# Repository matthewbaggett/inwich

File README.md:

# inwich
A PCB and software to allow a PC to push joypad commands to a console via USB.

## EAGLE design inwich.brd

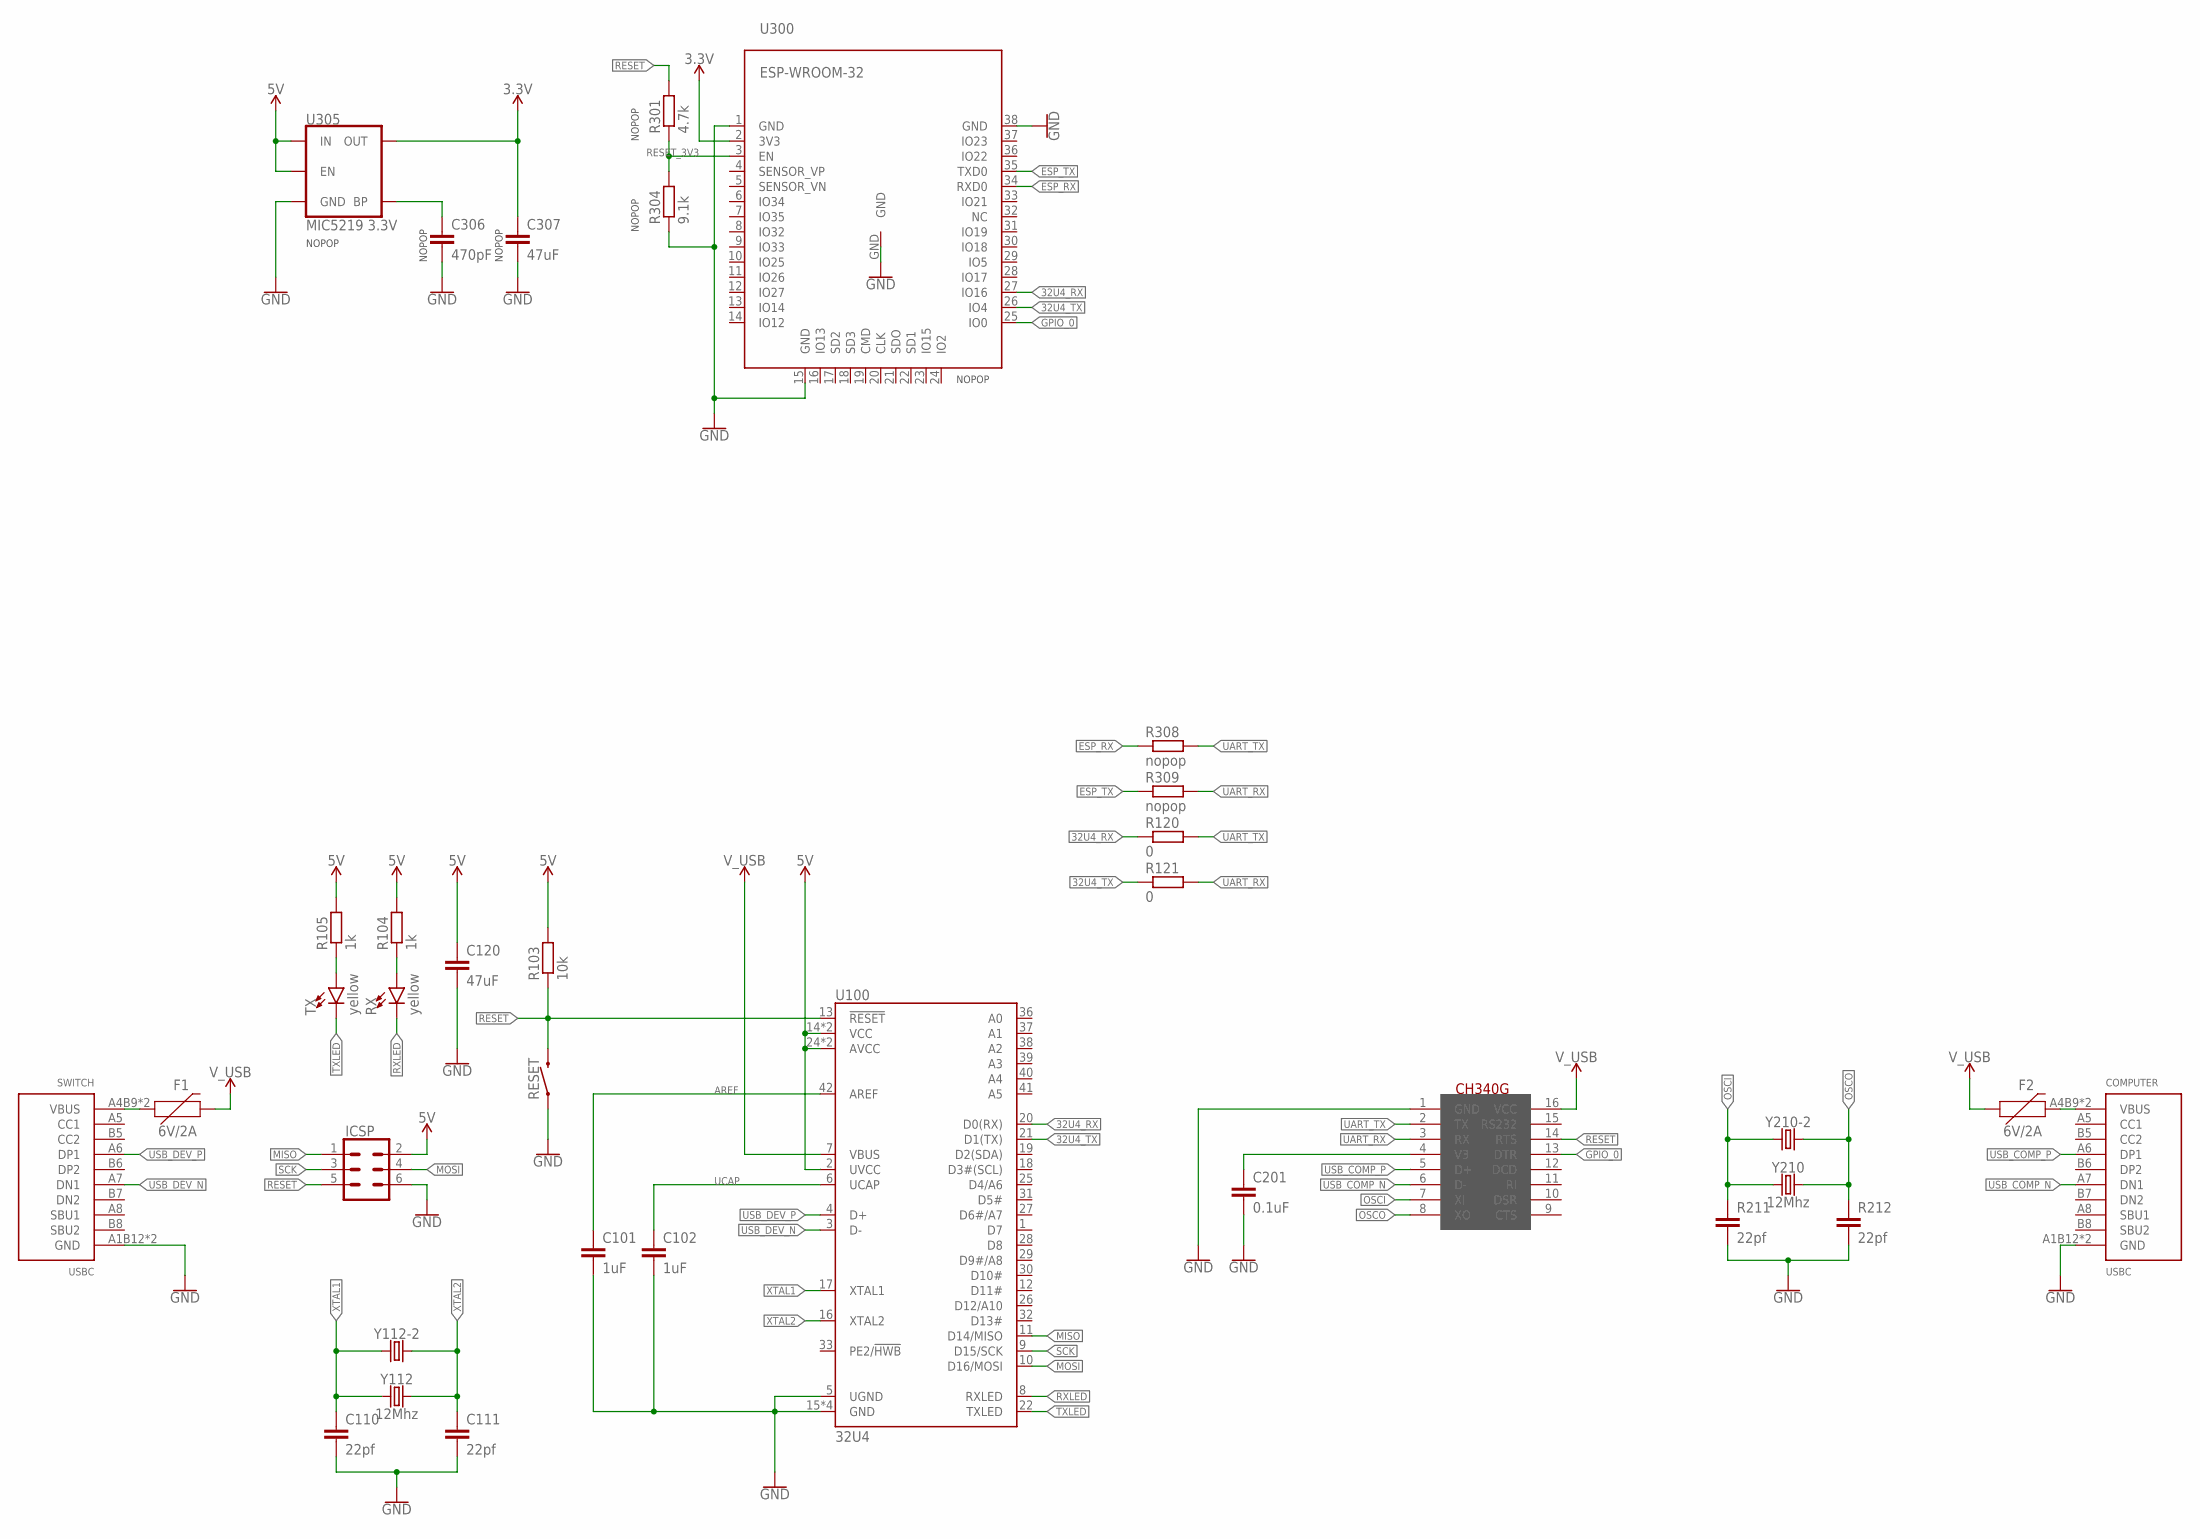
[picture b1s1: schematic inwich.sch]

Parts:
C101, C102: 1uF; C0805
C110, C111: 22pf; C0805
C120, C307: 47uF; C0805
C201: 0.1uF; C0805
C306: 470pF; C0805
COMPUTER: USBC
F1, F2: 6V/2A; 1210
ICSP: CONN_03X2SHROUD; 2X3-SHROUDED
R103: 10k; R0805
R104, R105: 1k; R0805
R120, R121: 0; R0805
R211, R212: 22pf; C0805
R301: 4.7k; R0805
R304: 9.1k; R0805
R308, R309: nopop; R0805
RESET: MOMENTARY-SWITCH-SPST-SMD-6.0X3.5MM; TACTILE_SWITCH_SMD_6.0X3.5MM
RX: yellow; LED-1206
SWITCH: USBC
TX: yellow; LED-1206
U100: 32U4; TQFP44
U200: CH340G; SOIC16
U300: ESP-WROOM-32
U305: MIC5219 3.3V; SOT23-5
Y112, Y210: 12Mhz; HC49UP
Y112-2, Y210-2: CRYSTALPTH-HC49UV; HC49U

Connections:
3.3V: C307.1, U300.2 (3V3), U305.5 (OUT)
5V: C120.1, ICSP.2, R103.2, R104.2, R105.2, U100.2 (UVCC), U100.14 (VCC), U100.24 (AVCC), U100.34 (VCC), U100.44 (AVCC), U305.1 (IN), U305.3 (EN)
32U4_RX: R120.1, U100.20 (D0(RX)), U300.27 (IO16)
32U4_TX: R121.1, U100.21 (D1(TX)), U300.26 (IO4)
AREF: C101.1, U100.42 (AREF)
ESP_RX: R308.1, U300.34 (RXD0)
ESP_TX: R309.1, U300.35 (TXD0)
GND: C101.2, C102.2, C110.2, C111.2, C120.2, C201.2, C306.2, C307.2, COMPUTER.A1B12 (GND), COMPUTER.B1A12 (GND), ICSP.6, R211.2, R212.2, R304.1, RESET.1, SWITCH.A1B12 (GND), SWITCH.B1A12 (GND), U100.5 (UGND), U100.15 (GND), U100.23 (GND), U100.35 (GND), U100.43 (GND), U200.1 (GND), U300.1 (GND), U300.15 (GND), U300.38 (GND), U300.GND, U305.2 (GND)
GPIO_0: U200.13 (DTR), U300.25 (IO0)
MISO: ICSP.1, U100.11 (D14/MISO)
MOSI: ICSP.4, U100.10 (D16/MOSI)
unnamed: R105.1, TX.A
unnamed: R104.1, RX.A
unnamed: C201.1, U200.4 (V3)
unnamed: C306.1, U305.4 (BP)
OSCI: R211.1, U200.7 (XI), Y210.1, Y210-2.1
OSCO: R212.1, U200.8 (XO), Y210.2, Y210-2.2
RESET: ICSP.5, R103.1, R301.2, RESET.2, U100.13 (!RESET), U200.14 (RTS)
RESET_3V3: R301.1, R304.2, U300.3 (EN)
RXLED: RX.C, U100.8 (RXLED)
SCK: ICSP.3, U100.9 (D15/SCK)
TXLED: TX.C, U100.22 (TXLED)
UART_RX: R121.2, R309.2, U200.3 (RX)
UART_TX: R120.2, R308.2, U200.2 (TX)
UCAP: C102.1, U100.6 (UCAP)
USB_COMP_N: COMPUTER.A7 (DN1), U200.6 (D-)
USB_COMP_P: COMPUTER.A6 (DP1), U200.5 (D+)
USB_DEV_N: SWITCH.A7 (DN1), U100.3 (D-)
USB_DEV_P: SWITCH.A6 (DP1), U100.4 (D+)
VUSB_COMP: COMPUTER.A4B9 (VBUS), COMPUTER.B4A9 (VBUS), F2.2
V_USB: F1.2, F2.1, U100.7 (VBUS), U200.16 (VCC)
V_USB_DEV: F1.1, SWITCH.A4B9 (VBUS), SWITCH.B4A9 (VBUS)
XTAL1: C110.1, U100.17 (XTAL1), Y112.1, Y112-2.1
XTAL2: C111.1, U100.16 (XTAL2), Y112.2, Y112-2.2

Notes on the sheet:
NOPOP

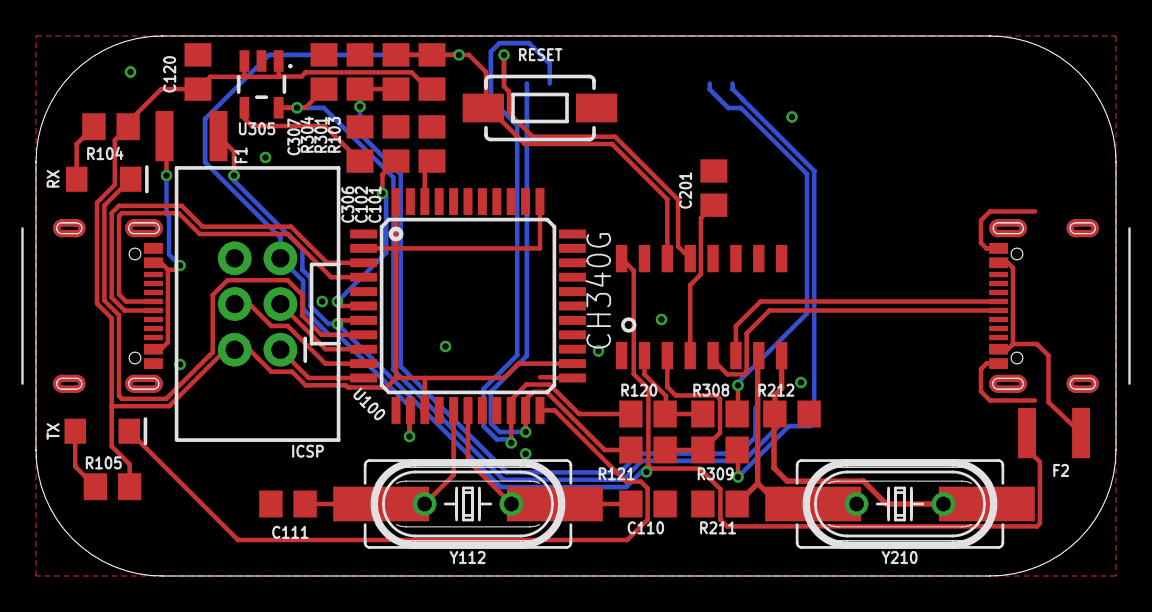
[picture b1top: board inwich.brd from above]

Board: 2 copper layers, 60.0 x 30.0 mm, 35 parts (1 on the bottom side), 34 nets.

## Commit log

2020-03-31 initial schematic and board

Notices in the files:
parts and their libraries:
SparkFun-Fuses: Licensing: Creative Commons ShareAlike 4.0 International - https://creativecommons.org/licenses/by-sa/4.0
